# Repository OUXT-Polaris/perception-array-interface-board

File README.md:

# perception-array-interface-board

## Overview

This is one of the boards that comprise the sensor unit for the RobotX2022 under development by OUXT. This sensor unit is a  "Perception Array", which is a hardware integration of two visible light cameras and a LiDAR (VLP-16) for sensor fusion. This board is installed in a box that relays the LAN and power cables of these three sensors.

KiCAD ( https://www.kicad.org/ ) is used for circuit design and PCB layout.

## CAD

### Version

KiCAD 5.1.7

### Parts Library

The symbol libraries and footprint libraries used in this schematic and PCB layout are basically KiCAD standard libraries, but some of them are in the following repositories.

https://github.com/alnicomag/kicad-custom-lib

## PCB rendering image

## Schematics

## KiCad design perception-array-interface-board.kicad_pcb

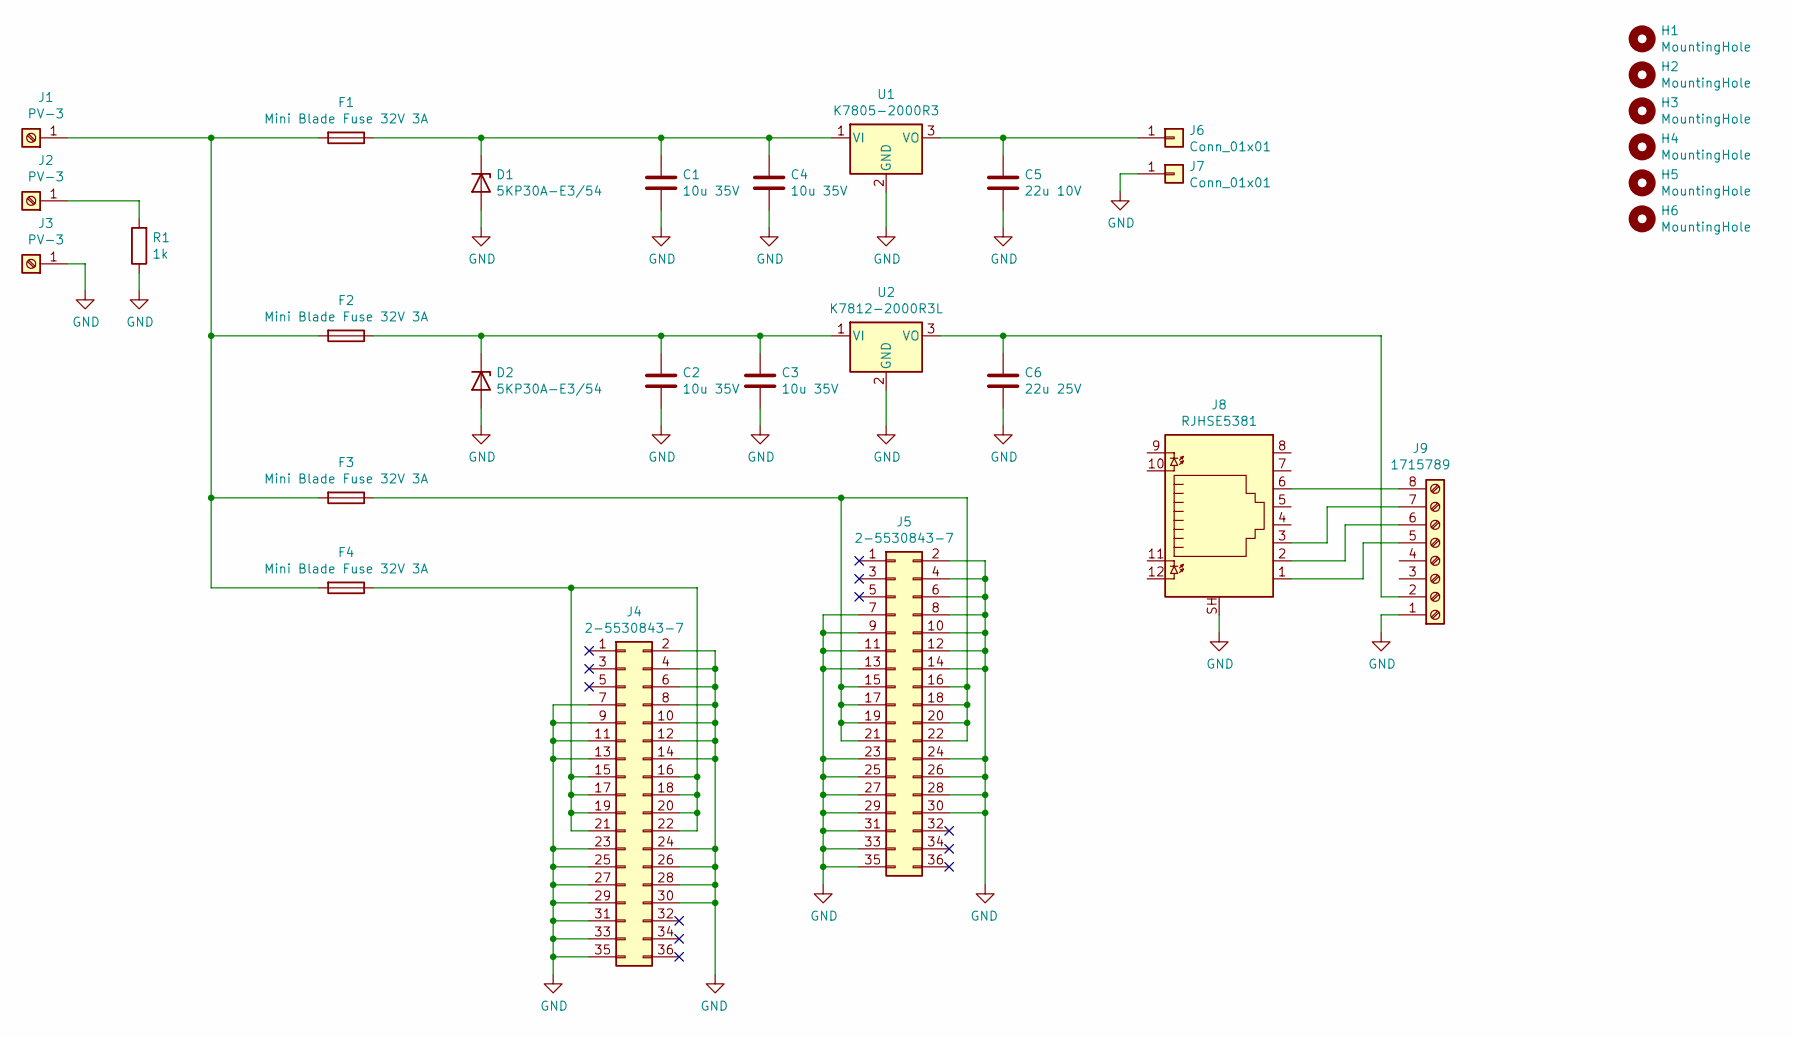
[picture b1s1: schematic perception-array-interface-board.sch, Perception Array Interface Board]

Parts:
C1, C2, C3, C4: 10u 35V; C_0805_2012Metric_Pad1.18x1.45mm_HandSolder
C5: 22u 10V; C_1206_3216Metric_Pad1.42x1.75mm_HandSolder
C6: 22u 25V; C_1206_3216Metric_Pad1.42x1.75mm_HandSolder
D1, D2: 5KP30A-E3/54; D_P600_R-6_P7.62mm_Vertical_KathodeUp
F1, F2, F3, F4: Mini Blade Fuse 32V 3A; RSPRO_1884617_plus_fuse
H1, H2, H3, H4, H5, H6: MountingHole; MountingHole_2.7mm_M2.5
J1, J2: PV-3
J3: PV-3; PV-3_via
J4, J5: 2-5530843-7; TE-Connectivity_2-5530843-7
J6, J7: Conn_01x01; Pin_D1.4mm_L8.5mm_W2.8mm_FlatFork
J8: RJHSE5381; RJ45_Amphenol_RJHSE538X
J9: 1715789; TerminalBlock_Phoenix_MKDS-1,5-8-5.08_1x08_P5.08mm_Horizont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
R1: 1k; R_0603_1608Metric_Pad1.05x0.95mm_HandSolder
U1: K7805-2000R3; RSPRO_K78xx-2000R3
U2: K7812-2000R3L; RSPRO_K78xx-2000R3L

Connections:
GND: C1.2, C2.2, C3.2, C4.2, C5.2, C6.2, D1.2 (A), D2.2 (A), J3.1, J4.2, J4.4, J4.6, J4.7, J4.8, J4.9, J4.10, J4.11, J4.12, J4.13, J4.14, J4.23, J4.24, J4.25, J4.26, J4.27, J4.28, J4.29, J4.30, J4.31, J4.33, J4.35, J5.2, J5.4, J5.6, J5.7, J5.8, J5.9, J5.10, J5.11, J5.12, J5.13, J5.14, J5.23, J5.24, J5.25, J5.26, J5.27, J5.28, J5.29, J5.30, J5.31, J5.33, J5.35, J7.1, J8.SH, J9.1, R1.1, U1.2 (GND), U2.2 (GND)
unnamed: C1.1, C4.1, D1.1 (K), F1.1, U1.1 (VI)
unnamed: C2.1, C3.1, D2.1 (K), F2.1, U2.1 (VI)
unnamed: C5.1, J6.1, U1.3 (VO)
unnamed: C6.1, J9.2, U2.3 (VO)
unnamed: F1.2, F2.2, F3.2, F4.2, J1.1
unnamed: F3.1, J5.15, J5.16, J5.17, J5.18, J5.19, J5.20, J5.21, J5.22
unnamed: F4.1, J4.15, J4.16, J4.17, J4.18, J4.19, J4.20, J4.21, J4.22
unnamed: J2.1, R1.2
unnamed: J8.1, J9.5
unnamed: J8.2, J9.6
unnamed: J8.3, J9.7
unnamed: J8.6, J9.8

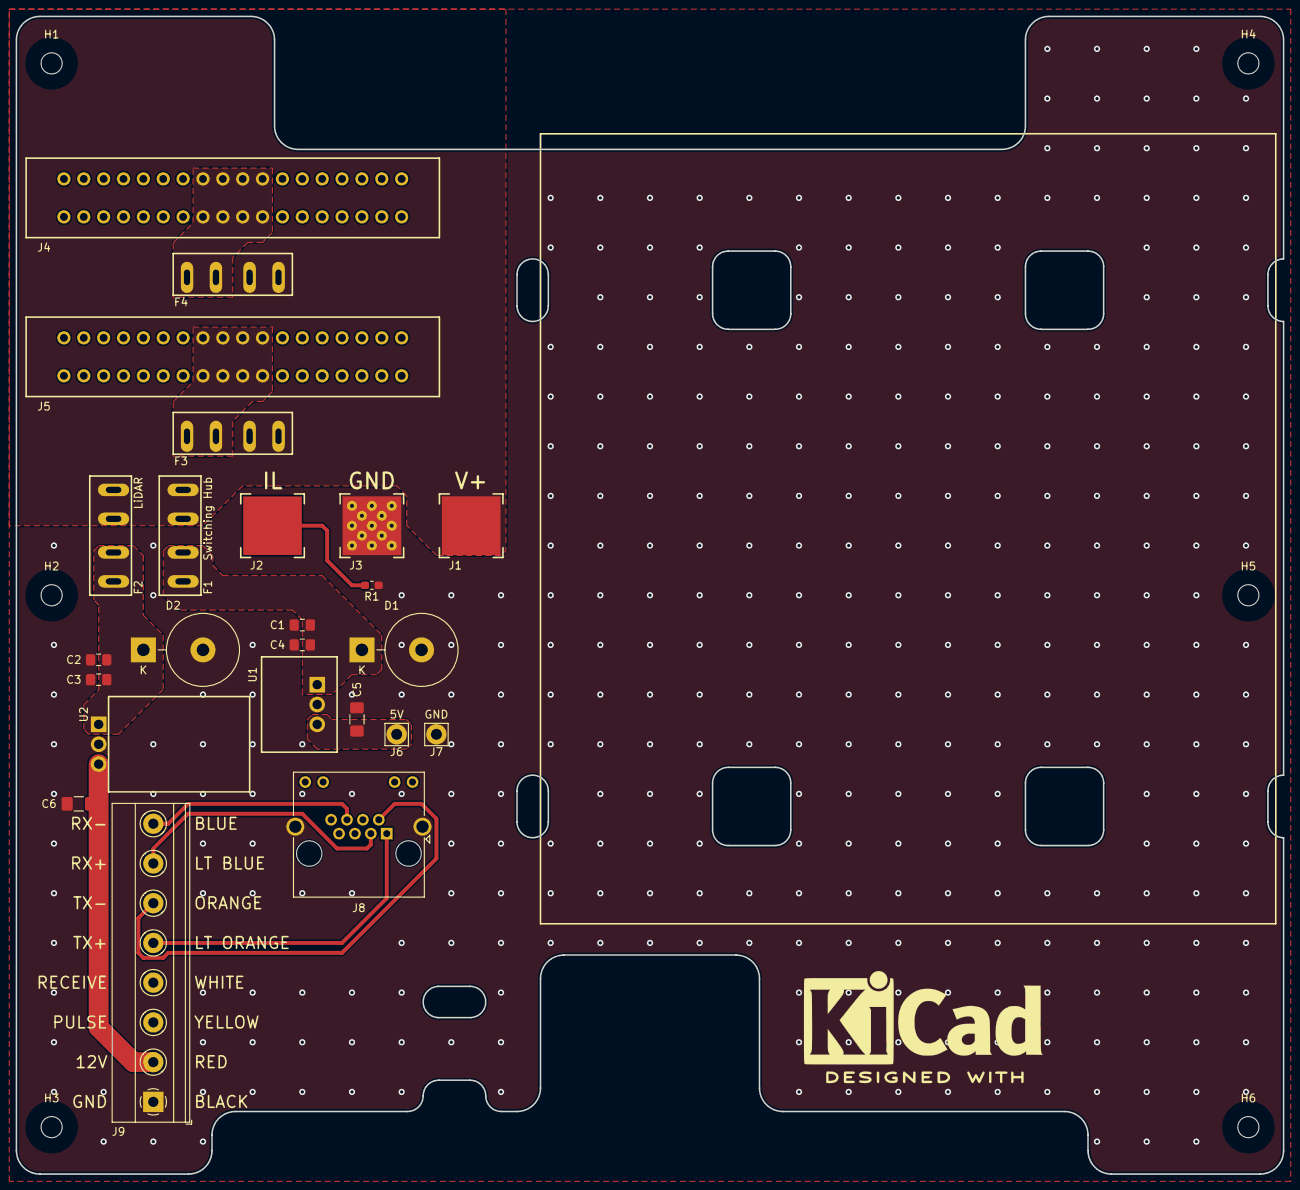
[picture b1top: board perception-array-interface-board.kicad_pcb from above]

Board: 2 copper layers, 162.0 x 148.0 mm, 30 parts (0 on the bottom side), 13 nets.

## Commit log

2021-06-17 Add kicad files
2021-06-17 Add pcb image file
2021-06-19 Update pcb layout
2021-06-22 Update schematics and layout
2021-06-22 Remove step file
2021-06-22 Update library table
2021-07-10 Update kicad files
2021-08-13 Update schematics
